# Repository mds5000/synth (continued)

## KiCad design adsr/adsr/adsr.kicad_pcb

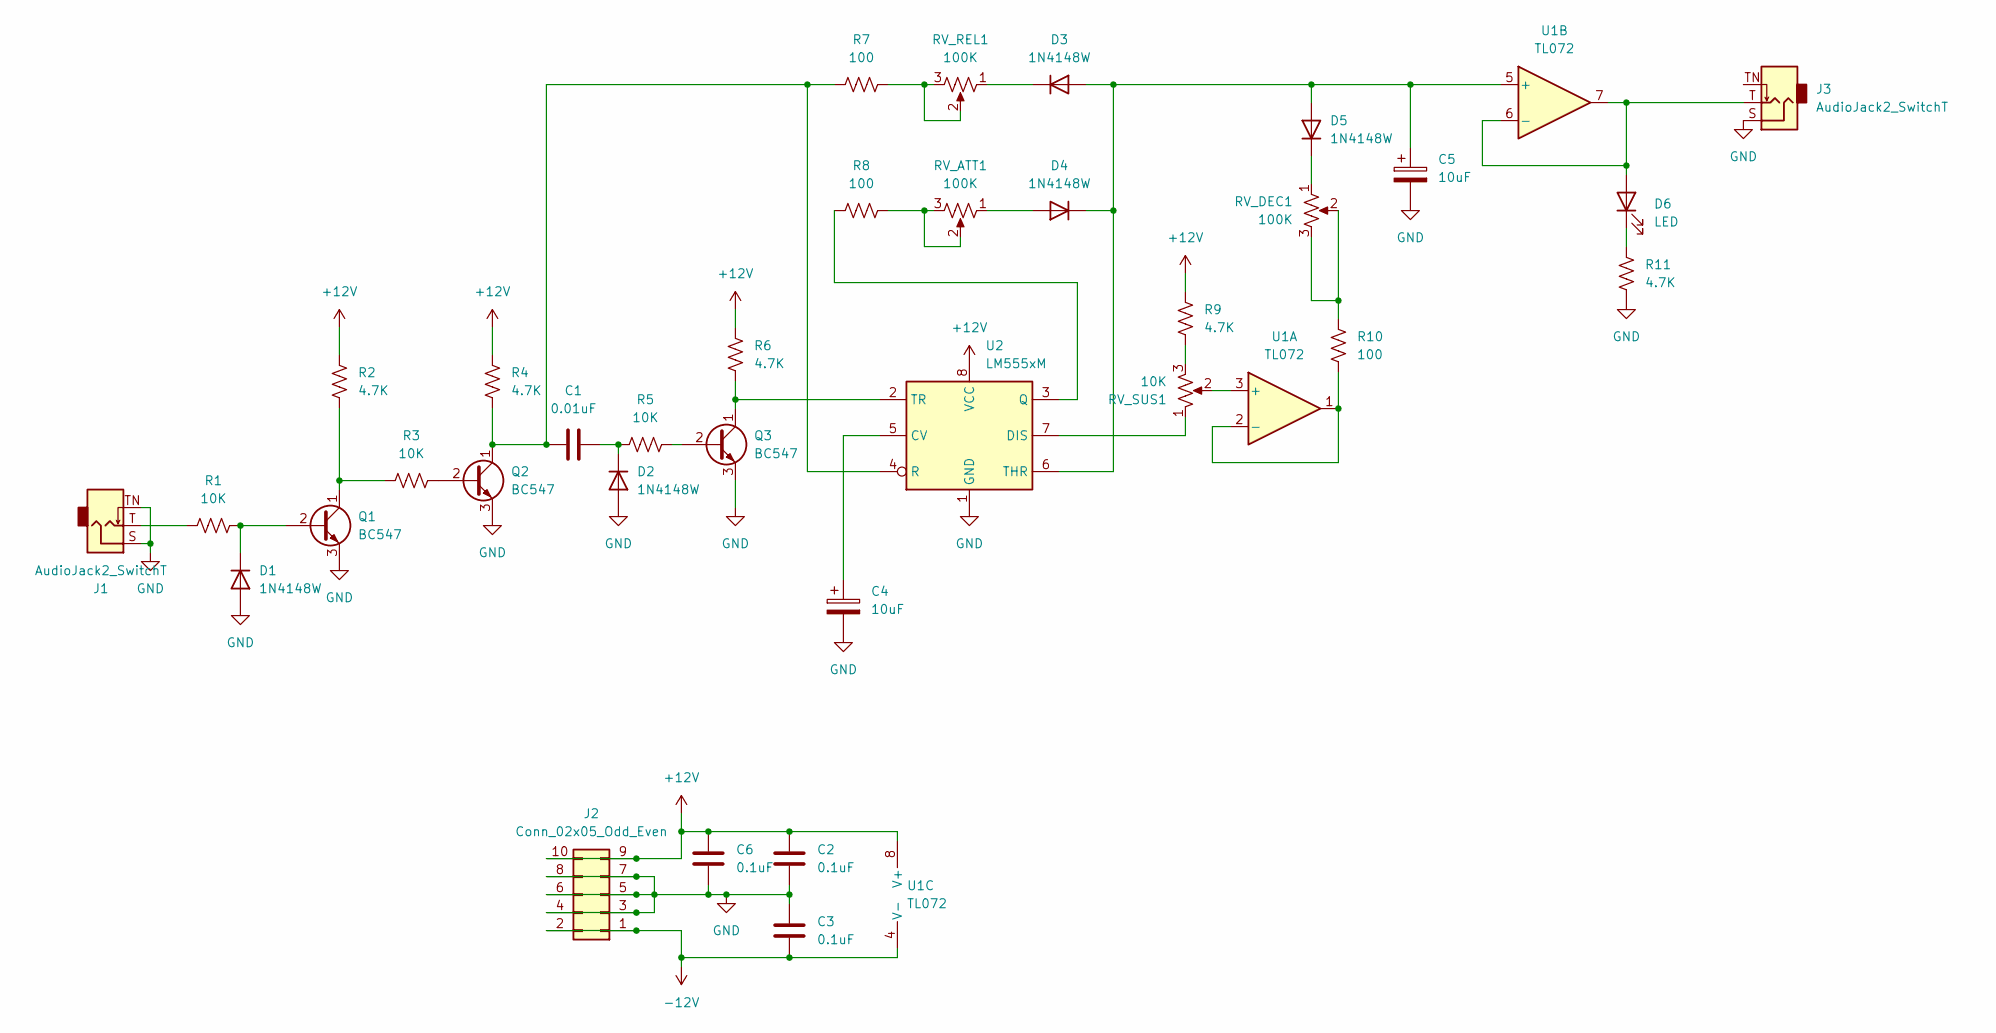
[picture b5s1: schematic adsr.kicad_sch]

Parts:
C1: 0.01uF; C_0603_1608Metric_Pad1.08x0.95mm_HandSolder
C2, C3, C6: 0.1uF; C_0603_1608Metric_Pad1.08x0.95mm_HandSolder
C4, C5: 10uF; CP_Radial_D5.0mm_P2.00mm
D1, D2, D3, D4, D5: 1N4148W; D_SOD-123
D6: LED; LED_D3.0mm
J1, J3: AudioJack2_SwitchT; Jack_3.5mm_QingPu_WQP-PJ398SM_Vertical_CircularHoles
J2: Conn_02x05_Odd_Even; PinHeader_2x05_P2.54mm_Vertical
Q1, Q2, Q3: BC547; TO-92_Inline
R1, R3, R5: 10K; R_0603_1608Metric_Pad0.98x0.95mm_HandSolder
R2, R4, R6, R9, R11: 4.7K; R_0603_1608Metric_Pad0.98x0.95mm_HandSolder
R7, R8, R10: 100; R_0603_1608Metric_Pad0.98x0.95mm_HandSolder
RV_ATT1: 100K; Potentiometer_Alpha_RD901F-40-00D_Single_Vertical
RV_DEC1: 100K; Potentiometer_Alpha_RD901F-40-00D_Single_Vertical
RV_REL1: 100K; Potentiometer_Alpha_RD901F-40-00D_Single_Vertical
RV_SUS1: 10K; Potentiometer_Alpha_RD901F-40-00D_Single_Vertical
U1: TL072; SOIC-8_3.9x4.9mm_P1.27mm
U2: LM555xM; SOIC-8_3.9x4.9mm_P1.27mm

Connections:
+12V: C2.1, C6.1, J2.9, J2.10, R2.1, R4.1, R6.1, R9.1, U1.8 (V+), U2.8 (VCC)
-12V: C3.2, J2.1, J2.2, U1.4 (V-)
GND: C2.2, C3.1, C4.2, C5.2, C6.2, D1.2 (A), D2.2 (A), J1.S, J1.TN, J2.3, J2.4, J2.5, J2.6, J2.7, J2.8, J3.S, Q1.3 (E), Q2.3 (E), Q3.3 (E), R11.2, U2.1 (GND)
unnamed: D1.1 (K), Q1.2 (B), R1.2
unnamed: C1.2, D2.1 (K), R5.1
unnamed: C5.1, D3.2 (A), D4.1 (K), D5.2 (A), U1.5 (+), U2.6 (THR)
unnamed: D3.1 (K), RV_REL1.1
unnamed: D4.2 (A), RV_ATT1.1
unnamed: D5.1 (K), RV_DEC1.1
unnamed: D6.2 (A), J3.T, U1.6 (-), U1.7
unnamed: D6.1 (K), R11.1
unnamed: J1.T, R1.1
unnamed: Q1.1 (C), R2.2, R3.1
unnamed: Q2.2 (B), R3.2
unnamed: C1.1, Q2.1 (C), R4.2, R7.1, U2.4 (R)
unnamed: Q3.2 (B), R5.2
unnamed: Q3.1 (C), R6.2, U2.2 (TR)
unnamed: R7.2, RV_REL1.2, RV_REL1.3
unnamed: R8.2, RV_ATT1.2, RV_ATT1.3
unnamed: R9.2, RV_SUS1.3
unnamed: R10.2, RV_DEC1.2, RV_DEC1.3
unnamed: RV_SUS1.2, U1.3 (+)
unnamed: R10.1, U1.1, U1.2 (-)
unnamed: C4.1, U2.5 (CV)
unnamed: RV_SUS1.1, U2.7 (DIS)
unnamed: R8.1, U2.3 (Q)

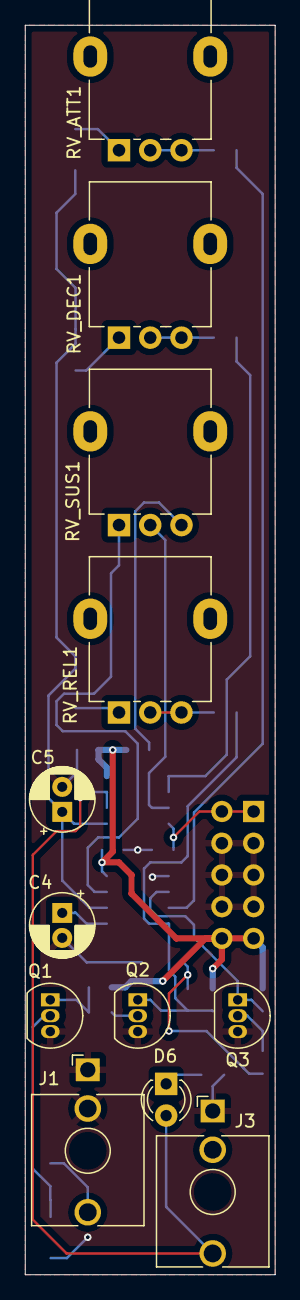
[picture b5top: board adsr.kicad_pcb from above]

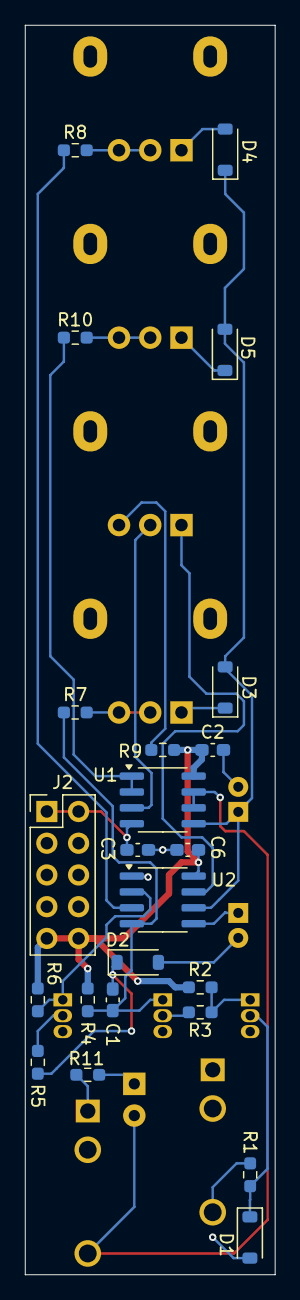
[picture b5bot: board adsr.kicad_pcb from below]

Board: 2 copper layers, 20.0 x 100.0 mm, 35 parts (23 on the bottom side), 26 nets.

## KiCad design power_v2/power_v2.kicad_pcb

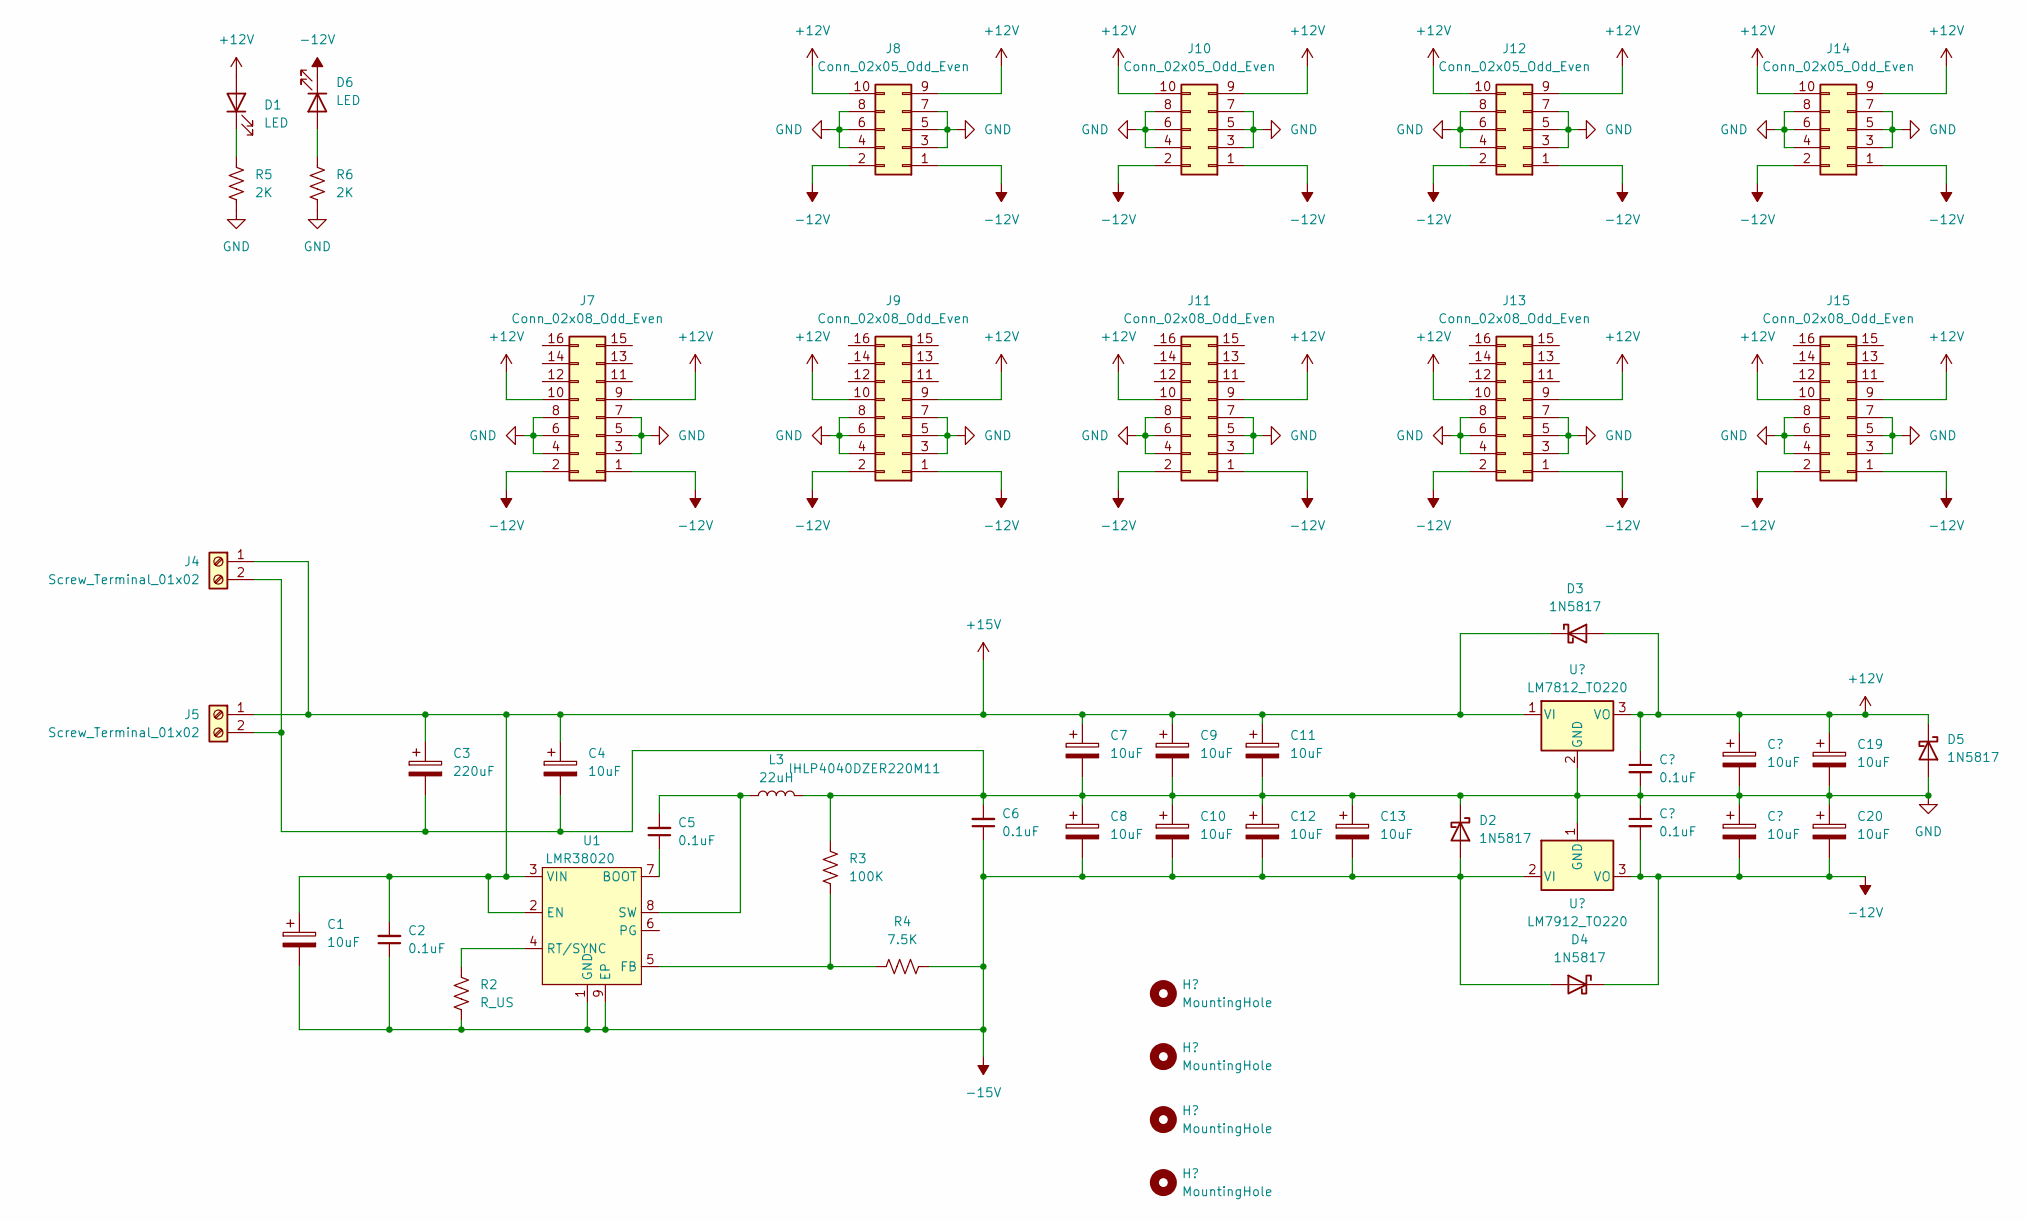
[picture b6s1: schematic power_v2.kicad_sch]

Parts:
C1, C4, C7, C8, C9, C10, C11, C12, C13, C17, C18, C19, C20: 10uF; C_1210_3225Metric_Pad1.33x2.70mm_HandSolder
C2, C5, C6, C15, C16: 0.1uF; C_0603_1608Metric
C3: 220uF; CP_Radial_D6.3mm_P2.50mm
D1, D6: LED; LED_0603_1608Metric_Pad1.05x0.95mm_HandSolder
D2, D3, D4, D5: 1N5817; D_SOD-123
H1, H2, H3, H4: MountingHole; MountingHole_3.2mm_M3_Pad
J4, J5: Screw_Terminal_01x02; TerminalBlock_Phoenix_PT-1,5-2-3.5-H_1x02_P3.50mm_Horizontal
J7, J9, J11, J13, J15: Conn_02x08_Odd_Even; PinHeader_2x08_P2.54mm_Vertical
J8, J10, J12, J14: Conn_02x05_Odd_Even; PinHeader_2x05_P2.54mm_Vertical
L3: 22uH; L_Vishay_IHLP-4040
R2: R_US; R_0603_1608Metric_Pad0.98x0.95mm_HandSolder
R3: 100K; R_0603_1608Metric_Pad0.98x0.95mm_HandSolder
R4: 7.5K; R_0603_1608Metric_Pad0.98x0.95mm_HandSolder
R5, R6: 2K; R_0603_1608Metric_Pad0.98x0.95mm_HandSolder
U1: SOIC-8-1EP_3.9x4.9mm_P1.27mm_EP2.29x3mm
U2: LM7812_TO220; TO-220-3_Horizontal_TabDown
U3: LM7912_TO220; TO-220-3_Horizontal_TabDown

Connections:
+12V: C15.1, C17.1, C19.1, D1.2 (A), D3.2 (A), D5.1 (K), J7.9, J7.10, J8.9, J8.10, J9.9, J9.10, J10.9, J10.10, J11.9, J11.10, J12.9, J12.10, J13.9, J13.10, J14.9, J14.10, J15.9, J15.10, U2.3 (VO)
+15V: C1.1, C2.2, C3.1, C4.1, C7.1, C9.1, C11.1, D3.1 (K), J4.1, J5.1, U1.2 (EN), U1.3 (VIN), U2.1 (VI)
-12V: C16.2, C18.2, C20.2, D4.1 (K), D6.1 (K), J7.1, J7.2, J8.1, J8.2, J9.1, J9.2, J10.1, J10.2, J11.1, J11.2, J12.1, J12.2, J13.1, J13.2, J14.1, J14.2, J15.1, J15.2, U3.3 (VO)
-15V: C1.2, C2.1, C6.1, C8.2, C10.2, C12.2, C13.2, D2.2 (A), D4.2 (A), R2.2, R4.2, U1.1 (GND), U1.9 (EP), U3.2 (VI)
GND: C3.2, C4.2, C6.2, C7.2, C8.1, C9.2, C10.1, C11.2, C12.1, C13.1, C15.2, C16.1, C17.2, C18.1, C19.2, C20.1, D2.1 (K), D5.2 (A), H1.1, H2.1, H3.1, H4.1, J4.2, J5.2, J7.3, J7.4, J7.5, J7.6, J7.7, J7.8, J8.3, J8.4, J8.5, J8.6, J8.7, J8.8, J9.3, J9.4, J9.5, J9.6, J9.7, J9.8, J10.3, J10.4, J10.5, J10.6, J10.7, J10.8, J11.3, J11.4, J11.5, J11.6, J11.7, J11.8, J12.3, J12.4, J12.5, J12.6, J12.7, J12.8, J13.3, J13.4, J13.5, J13.6, J13.7, J13.8, J14.3, J14.4, J14.5, J14.6, J14.7, J14.8, J15.3, J15.4, J15.5, J15.6, J15.7, J15.8, L3.2, R3.2, R5.2, R6.2, U2.2 (GND), U3.1 (GND)
unnamed: D1.1 (K), R5.1
unnamed: D6.2 (A), R6.1
unnamed: C5.1, U1.7 (BOOT)
unnamed: R3.1, R4.1, U1.5 (FB)
unnamed: R2.1, U1.4 (RT/SYNC)
unnamed: C5.2, L3.1, U1.8 (SW)

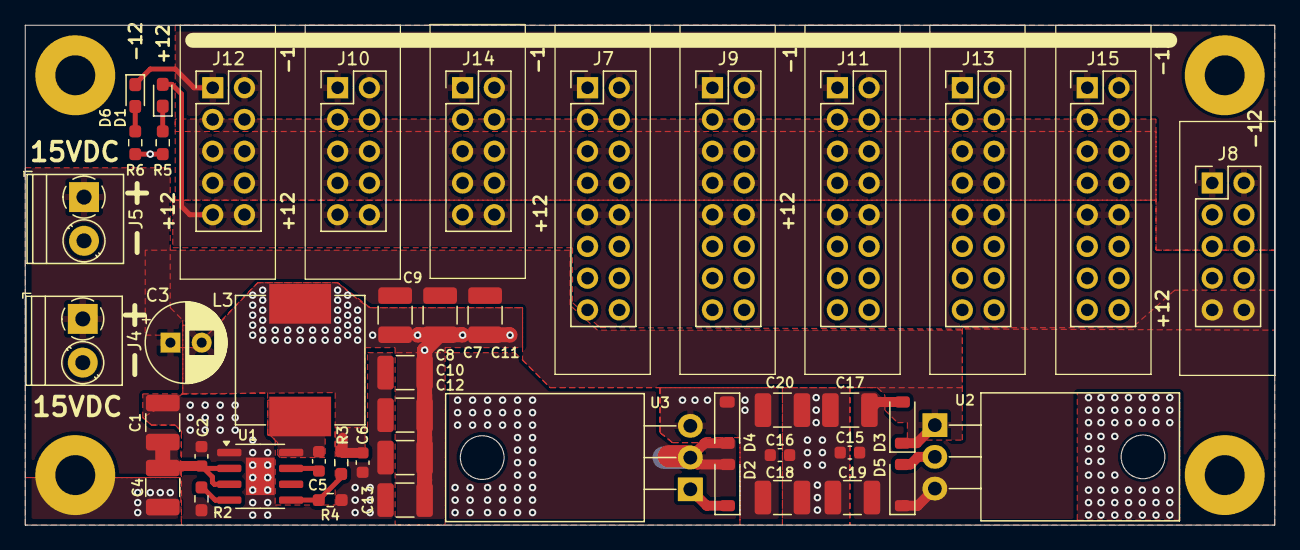
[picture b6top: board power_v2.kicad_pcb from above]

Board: 2 copper layers, 100.0 x 40.0 mm, 49 parts (0 on the bottom side), 11 nets.

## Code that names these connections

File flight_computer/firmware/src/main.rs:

#![no_std]
#![no_main]

use core::borrow::BorrowMut;

use embedded_hal_bus::spi::ExclusiveDevice;
use embedded_hal::digital::{OutputPin, StatefulOutputPin};
use rp235x_hal::{entry, fugit::RateExtU32, gpio::{Pin, FunctionPio0, FunctionSio, SioOutput, PullDown}, spi::SpiDevice};
use panic_halt as _;
use rp235x_hal as hal;
use embedded_hal::spi::MODE_0;

use hal::{
    pac,
    gpio,
    gpio::{PullNone, FunctionSpi},
    multicore::{Multicore, Stack},
   clocks::{init_clocks_and_plls, Clock},
   watchdog::Watchdog,
   Sio,
};
use ssd1351::{mode::GraphicsMode, prelude::SPIInterface};
use embedded_graphics::{geometry::{Point, Size}, primitives::StyledDrawable};
use embedded_graphics::{primitives::{PrimitiveStyleBuilder, Rectangle}};
use embedded_graphics::pixelcolor::{Rgb565, RgbColor};

use core::cell::RefCell;
use critical_section::Mutex;

mod output_core;

const XOSC_CRYSTAL_FREQ: u32 = 12_000_000u32;
static mut CORE1_STACK: Stack<4096> = Stack::new();
pub static LED: Mutex<RefCell<Option<Pin<hal::gpio::bank0::Gpio25, FunctionSio<SioOutput>, PullDown>>>> = Mutex::new(RefCell::new(None));

#[link_section = ".start_block"]
#[used]
pub static IMAGE_DEF: hal::block::ImageDef = hal::block::ImageDef::secure_exe();

#[entry]
fn main() -> ! {
    let mut pac = pac::Peripherals::take().unwrap();
    let core = cortex_m::Peripherals::take().unwrap();
    let mut watchdog = Watchdog::new(pac.WATCHDOG);

    let clocks = init_clocks_and_plls(
        XOSC_CRYSTAL_FREQ,
        pac.XOSC,
        pac.CLOCKS,
        pac.PLL_SYS,
        pac.PLL_USB,
        &mut pac.RESETS,
        &mut watchdog,
    )
    .ok()
    .unwrap();

    let mut delay = cortex_m::delay::Delay::new(core.SYST, clocks.system_clock.freq().to_Hz());
    let mut timer = hal::Timer::new_timer0(pac.TIMER0, &mut pac.RESETS, &clocks);

    let mut sio = Sio::new(pac.SIO);
    let pins = hal::gpio::Pins::new(
        pac.IO_BANK0,
        pac.PADS_BANK0,
        sio.gpio_bank0,
        &mut pac.RESETS,
    );

    let mut led_pin = pins.gpio25.into_push_pull_output();
    critical_section::with(|cs| LED.borrow(cs).replace(Some(led_pin)));

    // Setup PIO GPIO Pins
    let _dac1_sync: Pin<_, FunctionPio0, _> = pins.gpio16.into_function();
    let _dac1_clk: Pin<_, FunctionPio0, _> = pins.gpio17.into_function();
    let _dac1_data: Pin<_, FunctionPio0, _> = pins.gpio18.into_function();
    let _dac2_sync: Pin<_, FunctionPio0, _> = pins.gpio19.into_function();
    let _dac2_clk: Pin<_, FunctionPio0, _> = pins.gpio20.into_function();
    let _dac2_data: Pin<_, FunctionPio0, _> = pins.gpio21.into_function();
    let mut dac_rst = pins.gpio22.into_push_pull_output();
    dac_rst.set_high();

    let disp_clk: gpio::Pin<_, FunctionSpi, PullNone> = pins.gpio2.reconfigure();
    let disp_mosi: gpio::Pin<_, FunctionSpi, PullNone> = pins.gpio3.reconfigure();
    let disp_cs = pins.gpio5.into_push_pull_output();
    let mut disp_rst = pins.gpio6.into_push_pull_output();
    let disp_dc = pins.gpio7.into_push_pull_output();
    let mut disp_spi = hal::spi::Spi::<_,_,_,8>::new(pac.SPI0, (disp_mosi, disp_clk))
        .init(&mut pac.RESETS, clocks.system_clock.freq(), 50_000_000u32.Hz(), MODE_0);
    let disp_dev = ExclusiveDevice::new_no_delay(disp_spi, disp_cs).unwrap();
    let disp_if = SPIInterface::new(disp_dev, disp_dc);
    let mut disp: GraphicsMode<_> = ssd1351::builder::Builder::new()
        .with_rotation(ssd1351::properties::DisplayRotation::Rotate0)
        .with_size(ssd1351::properties::DisplaySize::Display128x128)
        .connect_interface(disp_if)
        .into();

    disp.reset(&mut disp_rst, &mut timer).unwrap();
    disp.init().unwrap();

    let style = PrimitiveStyleBuilder::new().fill_color(Rgb565::RED).build();


    let system_clk = clocks.system_clock.freq().to_Hz();
    let mut mc = Multicore::new(&mut pac.PSM, &mut pac.PPB, &mut sio.fifo);
    let cores = mc.cores();
    let core1 = &mut cores[1];
    core1.spawn(unsafe {&mut CORE1_STACK.mem}, output_core::core1_loop);


    loop {
        Rectangle::new(Point::new(0,0), Size::new(128, 128)).draw_styled(&style, &mut disp);
    }
}

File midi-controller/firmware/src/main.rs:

#![no_main]
#![no_std]

use embedded_midi::MidiMessage;
use panic_halt as _;

use hal::prelude::*;
use hal::stm32;
use hal::rcc::Config;
use hal::serial::FullConfig;
use stm32g4xx_hal::dac::DacExt;
use stm32g4xx_hal::dac::DacOut;
use stm32g4xx_hal::pwr::PwrExt;
use stm32g4xx_hal::time::{Bps, RateExtU32};
use stm32g4xx_hal as hal;

use embedded_midi::{MidiIn, Note};

use cortex_m_rt::entry;
use rtt_target::{rtt_init_print, rprintln, ChannelMode};

fn note_to_voltage(note: Note) -> u16 {
    let full_scale: f32 = 3.300_f32 * 3.0 * 1_000_000.0; //uv full-scale output;
    let codes = 4095.0;
    let uv_per_volt = 1_000_000_f32;
    let notes_per_octave = 12_f32;
    let codes_per_note: f32 = uv_per_volt / (full_scale / codes) / notes_per_octave;

    let note_number: u8 = note.into();
    let code = unsafe { ((note_number as f32) * codes_per_note).to_int_unchecked::<u16>() };
    let bias = 5;

    code + bias
}

#[entry]
fn main() -> ! {
    rtt_init_print!(ChannelMode::BlockIfFull);
    rprintln!("Started");

    let dp = stm32::Peripherals::take().expect("cannot take peripherals");
    let cp = cortex_m::Peripherals::take().expect("cannot take peripherals");
    let pwr = dp.PWR.constrain().freeze();
    let mut rcc = dp.RCC.constrain().freeze(Config::pll(), pwr);
    let mut delay = cp.SYST.delay(&rcc.clocks);

    let gpioa = dp.GPIOA.split(&mut rcc);
    let mut gate_1 = gpioa.pa7.into_push_pull_output();
    let mut _gate_2 = gpioa.pa6.into_push_pull_output();

    let mod_1_pin = gpioa.pa0.into_alternate();
    let mod_2_pin = gpioa.pa1.into_alternate();
    let (mut mod_1, mut mod_2) = dp.TIM2.pwm((mod_1_pin, mod_2_pin), 100.kHz(), &mut rcc);

    let (dac_ch1, dac_ch2) = dp.DAC1.constrain((gpioa.pa4, gpioa.pa5), &mut rcc);
    let mut cv_1 = dac_ch1.calibrate_buffer(&mut delay).enable();
    let mut cv_2 = dac_ch2.calibrate_buffer(&mut delay).enable();

    let tx = gpioa.pa2.into_alternate();
    let rx = gpioa.pa3.into_alternate();
    let midi_rx = dp.USART2.usart(tx, rx, FullConfig::default().baudrate(Bps(31250)), &mut rcc).unwrap();
    let mut midi = MidiIn::new(midi_rx);

    let gpiob = dp.GPIOB.split(&mut rcc);
    let mut led_1 = gpiob.pb8.into_push_pull_output();
    let mut led_2 = gpiob.pb7.into_push_pull_output();

    led_2.set_high().unwrap();
    cv_1.set_value(2048);
    cv_2.set_value(1024);
    loop {
        if let Ok(msg) = midi.read() {
            match msg {
                MidiMessage::TimingClock => {
                    led_2.toggle().unwrap();
                }
                MidiMessage::NoteOn(_, note, _) => {
                    led_1.set_high().unwrap();
                    gate_1.set_high().unwrap();
                    let value = note_to_voltage(note);
                    cv_1.set_value(value);
                    //rprintln!("NOTE ON: {:?} -> {}", note, value)
                },
                MidiMessage::NoteOff(_, _note, _) => {
                    led_1.set_low().unwrap();
                    gate_1.set_low().unwrap();
                    //rprintln!("NOTE OFF: {:?}", note)
                },
                MidiMessage::ControlChange(_, ch, value) => {
                    let v: u8 = value.into();
                    match ch.into() {
                        0 => mod_1.set_duty(mod_1.get_max_duty() / 128 * (v as u32)),
                        1 => mod_2.set_duty(mod_2.get_max_duty() / 128 * (v as u32)),
                        _ => {}
                    }
                    //rprintln!("PARAM CHG: {:?}: {:?}", ch, value),
                },

                unhandled_msg => rprintln!("OTHER: {:?}", unhandled_msg),
            }
        }
    }
}

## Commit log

2025-04-16 Added flight computer display
